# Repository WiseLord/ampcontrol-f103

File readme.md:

# Ampcontrol (STM32F103 / F303 version)

Ampcontrol is an control module for your DIY audio amplifier.
It supports various I²C-controlled audioprocessors and FM tuners.
Also, some other third-party devices are supported.

Some videos related to the device can be found at
[Youtube](https://www.youtube.com/playlist?list=PLfv57leyFFd1C61HgnKE3e_OFIXMBtf-D)

## Hardware support

- Graphic color TFT displays based on various controllers:
  - 160x128: ILI9163, S6D0144, ST7735;
  - 176x132: L2F50126, LPH9157, LS020, SSD1286A;
  - 220x176: HX8340, ILI9225, LGDP4524, S6D0164;
  - 320x240: HX8347A, HX8347D, ILI9320, ILI9341, MC2PA8201, S6D0129, S6D0139, SPFD5408, SSD1289, SSD2119;
  - 400x240: ILI9327, S6D04D1, ST7793;
  - 480x320: HX8357C, ILI9481, ILI9486, R61581, RM68140, ST7796S.

- Audio processors with I²C bus:
  - TDA7439, TDA731X, PT232X, TDA7418, TDA7719.

- FM tuners with I²C bus:
  - RDA580X, SI470X, TEA5767.

- Bluetooth modules
  - CSR8645, BK8000L (GPIO-based control via PCF8574x I²C expander);
  - BT201 (USART-based control).

- USB HID
  - Meida player on the PC can be controlled (Play/Pause and so on) by the device.

- KaRadio and MPD support
  - The device can act as "KaRadio plugin" via USART2 to add web radio support via ESP32. Alternatively, 
it can control MPD server running on Linux (for example, Raspberry PI).

More specific info can be found in [documentation](doc) pages.

## Building the code

[GNU Arm Embedded Toolchain](https://developer.arm.com/tools-and-software/open-source-software/developer-tools/gnu-toolchain/gnu-rm/downloads)
is required to build the project.

The project build system is based on [GNU Make](https://www.gnu.org/software/make/).
Linux users must have it already installed or they can easily do it.
For Windows users there is a port exists.
In both cases, both toolchain and make binaries should be added to the system PATH.

The process of building is very simple and doesn't depend on any other software installed.

### Default build (ILI9341 display with SPI wiring):

`make`

### Build for the specific STM32 MCUs, display and wiring:

`make STM32_MCU=F303CB DISPLAY=R61581 DISPVAR=8BIT`

The list of supported display controllers and MCUs can be found in Makefile or build_all.sh script.

## Schematics and wiring

The schematic and PCB files for the device itself in KiCad format can be found 
in [kicad/ampcontrol-f103](kicad/ampcontrol-f103) directory.

## Useful links

* [Firmware releases](https://github.com/WiseLord/ampcontrol-f103/releases)

* [The article (in Russian)](https://radiokot.ru/artfiles/6484/)

* [Forum thread (in Russian)](https://radiokot.ru/forum/viewtopic.php?f=2&t=158605)

* [Youtube playlist](https://www.youtube.com/playlist?list=PLfv57leyFFd1C61HgnKE3e_OFIXMBtf-D)

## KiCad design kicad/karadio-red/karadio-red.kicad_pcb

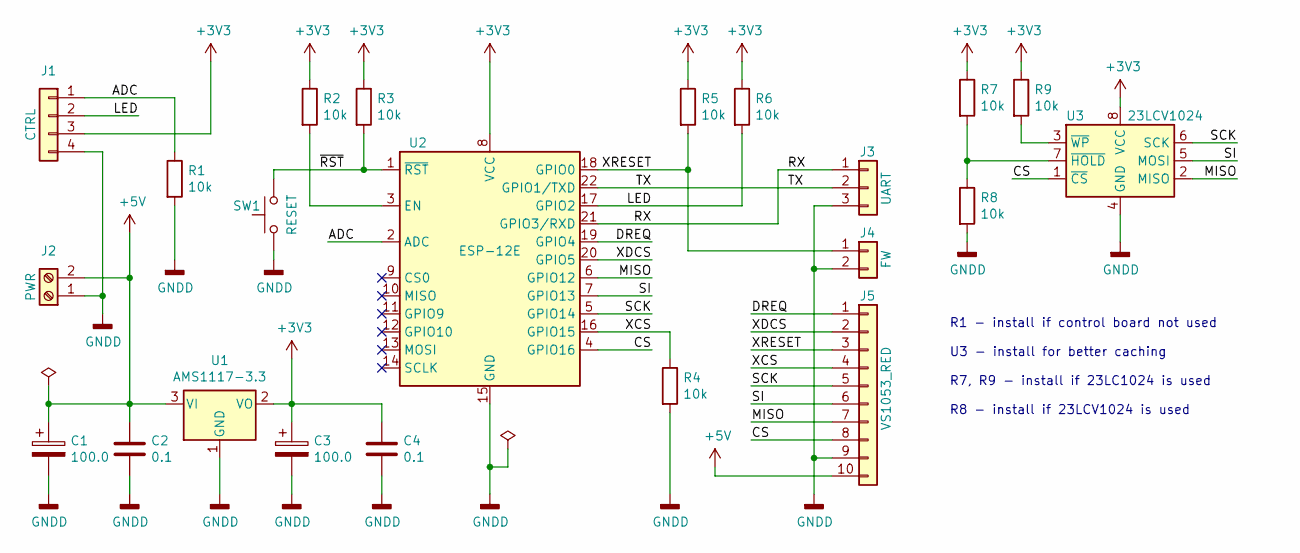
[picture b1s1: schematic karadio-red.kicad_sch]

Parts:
C1, C3: 100.0; CP_Radial_D6.3mm_P2.50mm
C2, C4: 0.1; C_1206_3216Metric
J1: CTRL; PinHeader_1x04_P2.54mm_Vertical
J2: PWR; TerminalBlock_bornier-2_P5.08mm
J3: UART; PinHeader_1x03_P2.54mm_Vertical
J4: FW; PinHeader_1x02_P2.54mm_Vertical
J5: VS1053_RED; PinSocket_1x10_P2.54mm_Vertical
R1, R2, R3, R4, R5, R6, R7, R8, R9: 10k; R_1206_3216Metric
SW1: RESET; SW_PUSH_6mm
U1: AMS1117-3.3; SOT-223-3_TabPin2
U2: ESP-12E
U3: 23LCV1024; SO-8_3.9x4.9mm_P1.27mm

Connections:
+3V3: C3.1, C4.1, J1.3, R2.1, R3.1, R5.1, R6.1, R7.1, R9.1, U1.2 (VO), U2.8 (VCC), U3.8 (VCC)
+5V: C1.1, C2.1, J2.2, J5.10, U1.3 (VI)
/ADC: J1.1, R1.1, U2.2 (ADC)
/CS: J5.8, U2.4 (GPIO16), U3.1 (~CS)
/DREQ: J5.1, U2.19 (GPIO4)
/LED: J1.2, R6.2, U2.17 (GPIO2)
/MISO: J5.7, U2.6 (GPIO12), U3.2 (MISO)
/RX: J3.1, U2.21 (GPIO3/RXD)
/SCK: J5.5, U2.5 (GPIO14), U3.6 (SCK)
/SI: J5.6, U2.7 (GPIO13), U3.5 (MOSI)
/TX: J3.2, U2.22 (GPIO1/TXD)
/XCS: J5.4, R4.1, U2.16 (GPIO15)
/XDCS: J5.2, U2.20 (GPIO5)
/XRESET: J4.1, J5.3, R5.2, U2.18 (GPIO0)
/~RST: R3.2, SW1.2, U2.1 (~RST)
GNDD: C1.2, C2.2, C3.2, C4.2, J1.4, J2.1, J3.3, J4.2, J5.9, R1.2, R4.2, R8.2, SW1.1, U1.1 (GND), U2.15 (GND), U3.4 (GND)
unnamed: R2.2, U2.3 (EN)
unnamed: R7.2, R8.1, U3.7 (~HOLD)
unnamed: R9.2, U3.3 (~WP)

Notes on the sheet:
R1 - install if control board not used U3 - install for better caching R7, R9 - install if 23LC1024 is used R8 - install if 23LCV1024 is used

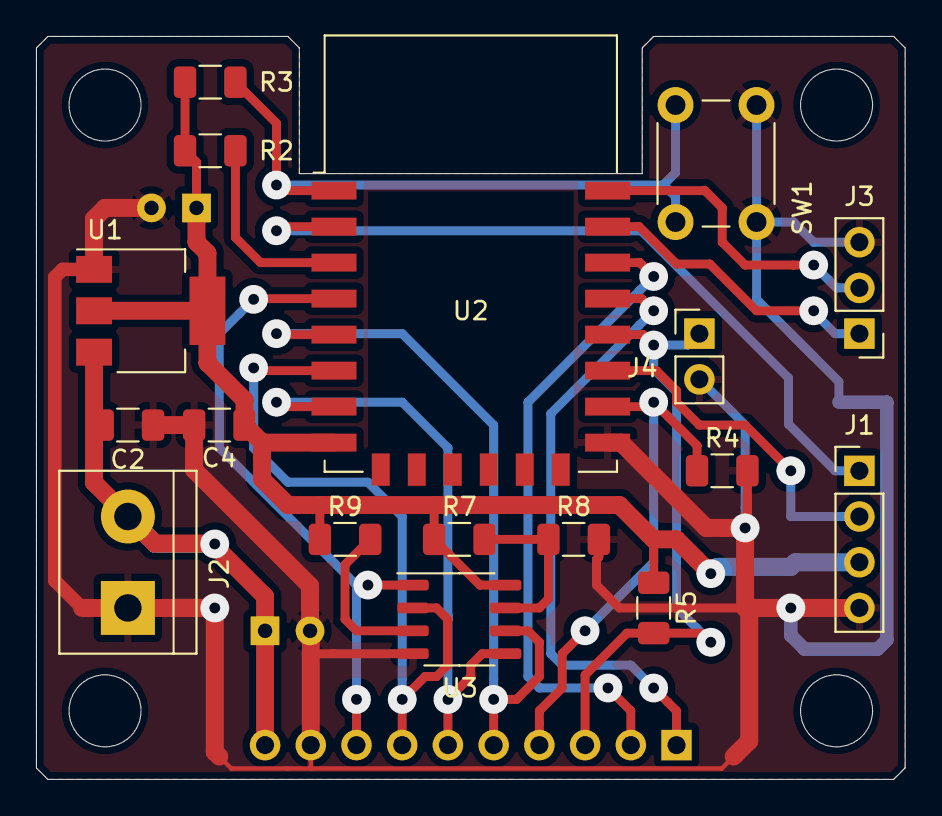
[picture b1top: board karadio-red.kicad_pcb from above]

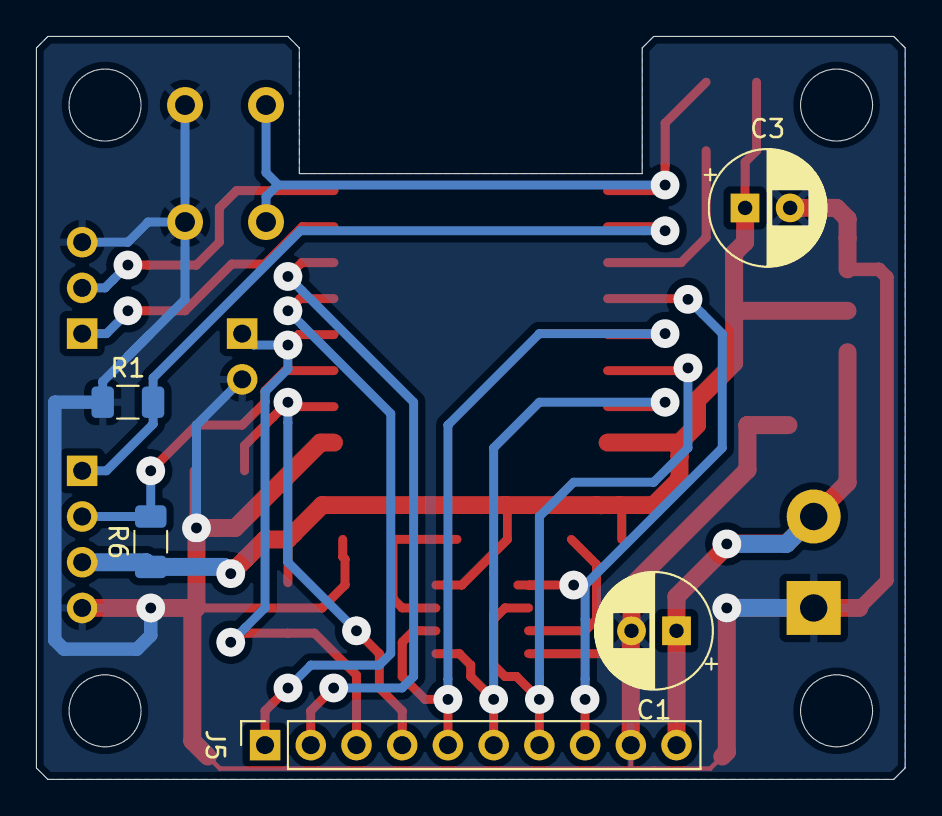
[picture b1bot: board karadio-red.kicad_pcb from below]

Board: 2 copper layers, 48.3 x 41.3 mm, 22 parts (5 on the bottom side), 19 nets.

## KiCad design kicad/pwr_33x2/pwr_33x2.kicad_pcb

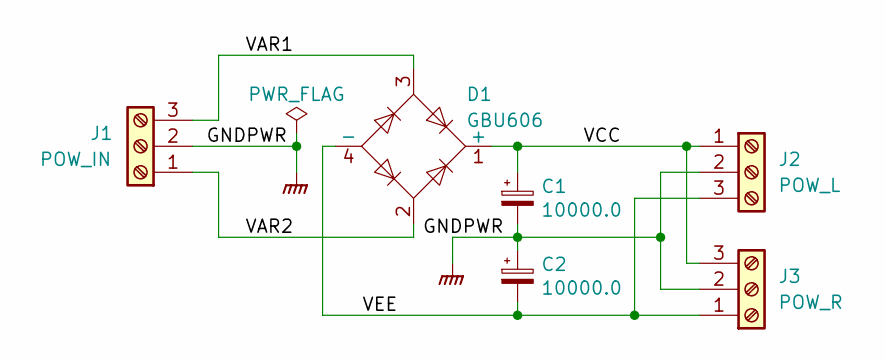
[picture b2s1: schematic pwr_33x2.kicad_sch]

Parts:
C1, C2: 10000.0; CP_Radial_D25.0mm_P10.00mm_SnapIn
D1: GBU606; Diode_Bridge_Vishay_GBU
J1: POW_IN; TerminalBlock_bornier-3_P5.08mm
J2: POW_L; TerminalBlock_bornier-3_P5.08mm
J3: POW_R; TerminalBlock_bornier-3_P5.08mm

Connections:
/VAR1: D1.3, J1.3
/VAR2: D1.2, J1.1
/VCC: C1.1, D1.1 (+), J2.1, J3.3
/VEE: C2.2, D1.4 (-), J2.3, J3.1
GNDPWR: C1.2, C2.1, J1.2, J2.2, J3.2

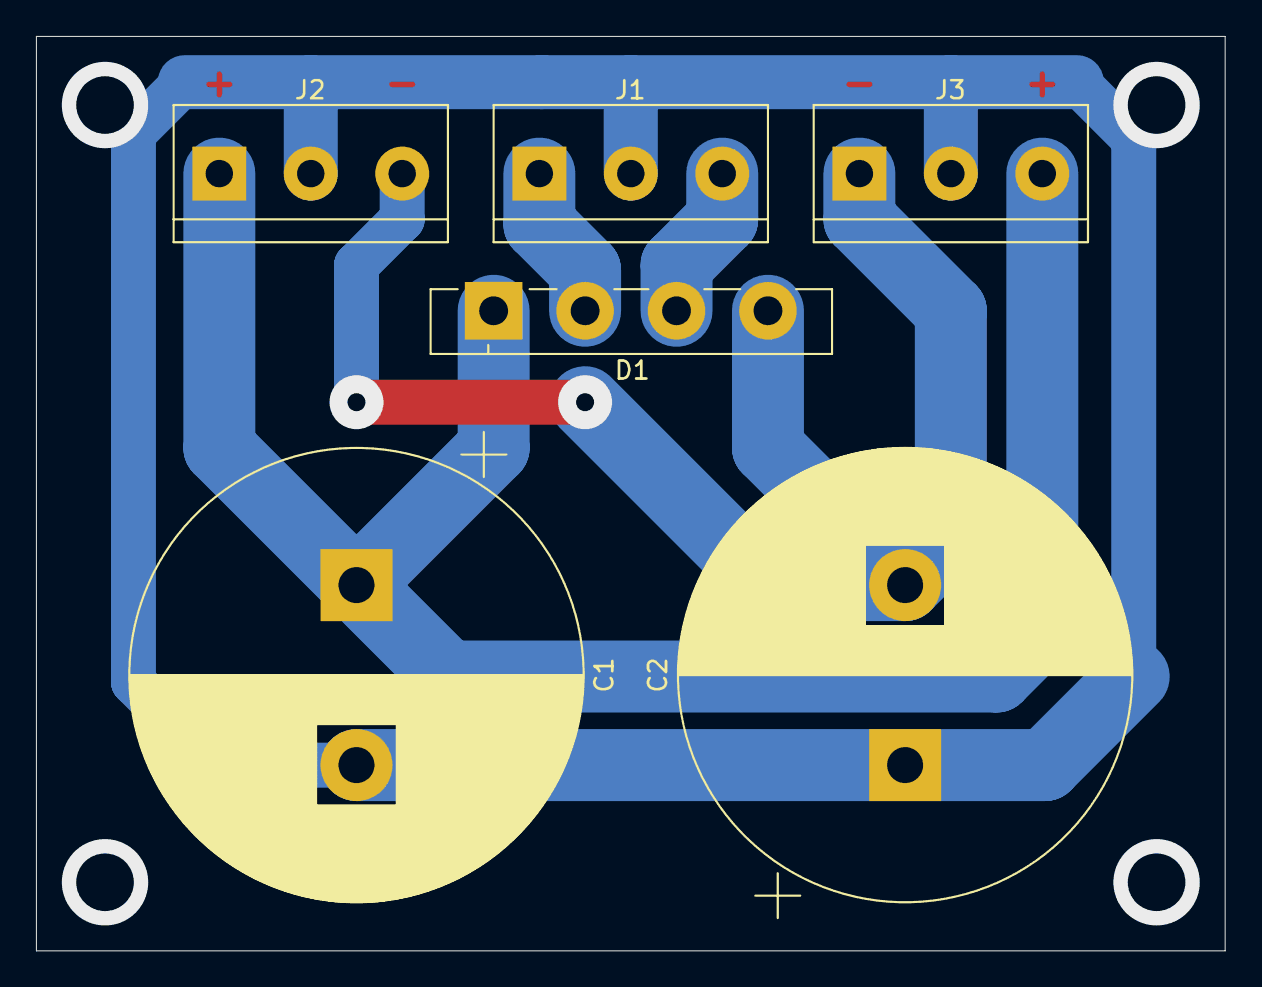
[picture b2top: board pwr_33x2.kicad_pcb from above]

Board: 2 copper layers, 66.0 x 50.8 mm, 6 parts (0 on the bottom side), 5 nets.

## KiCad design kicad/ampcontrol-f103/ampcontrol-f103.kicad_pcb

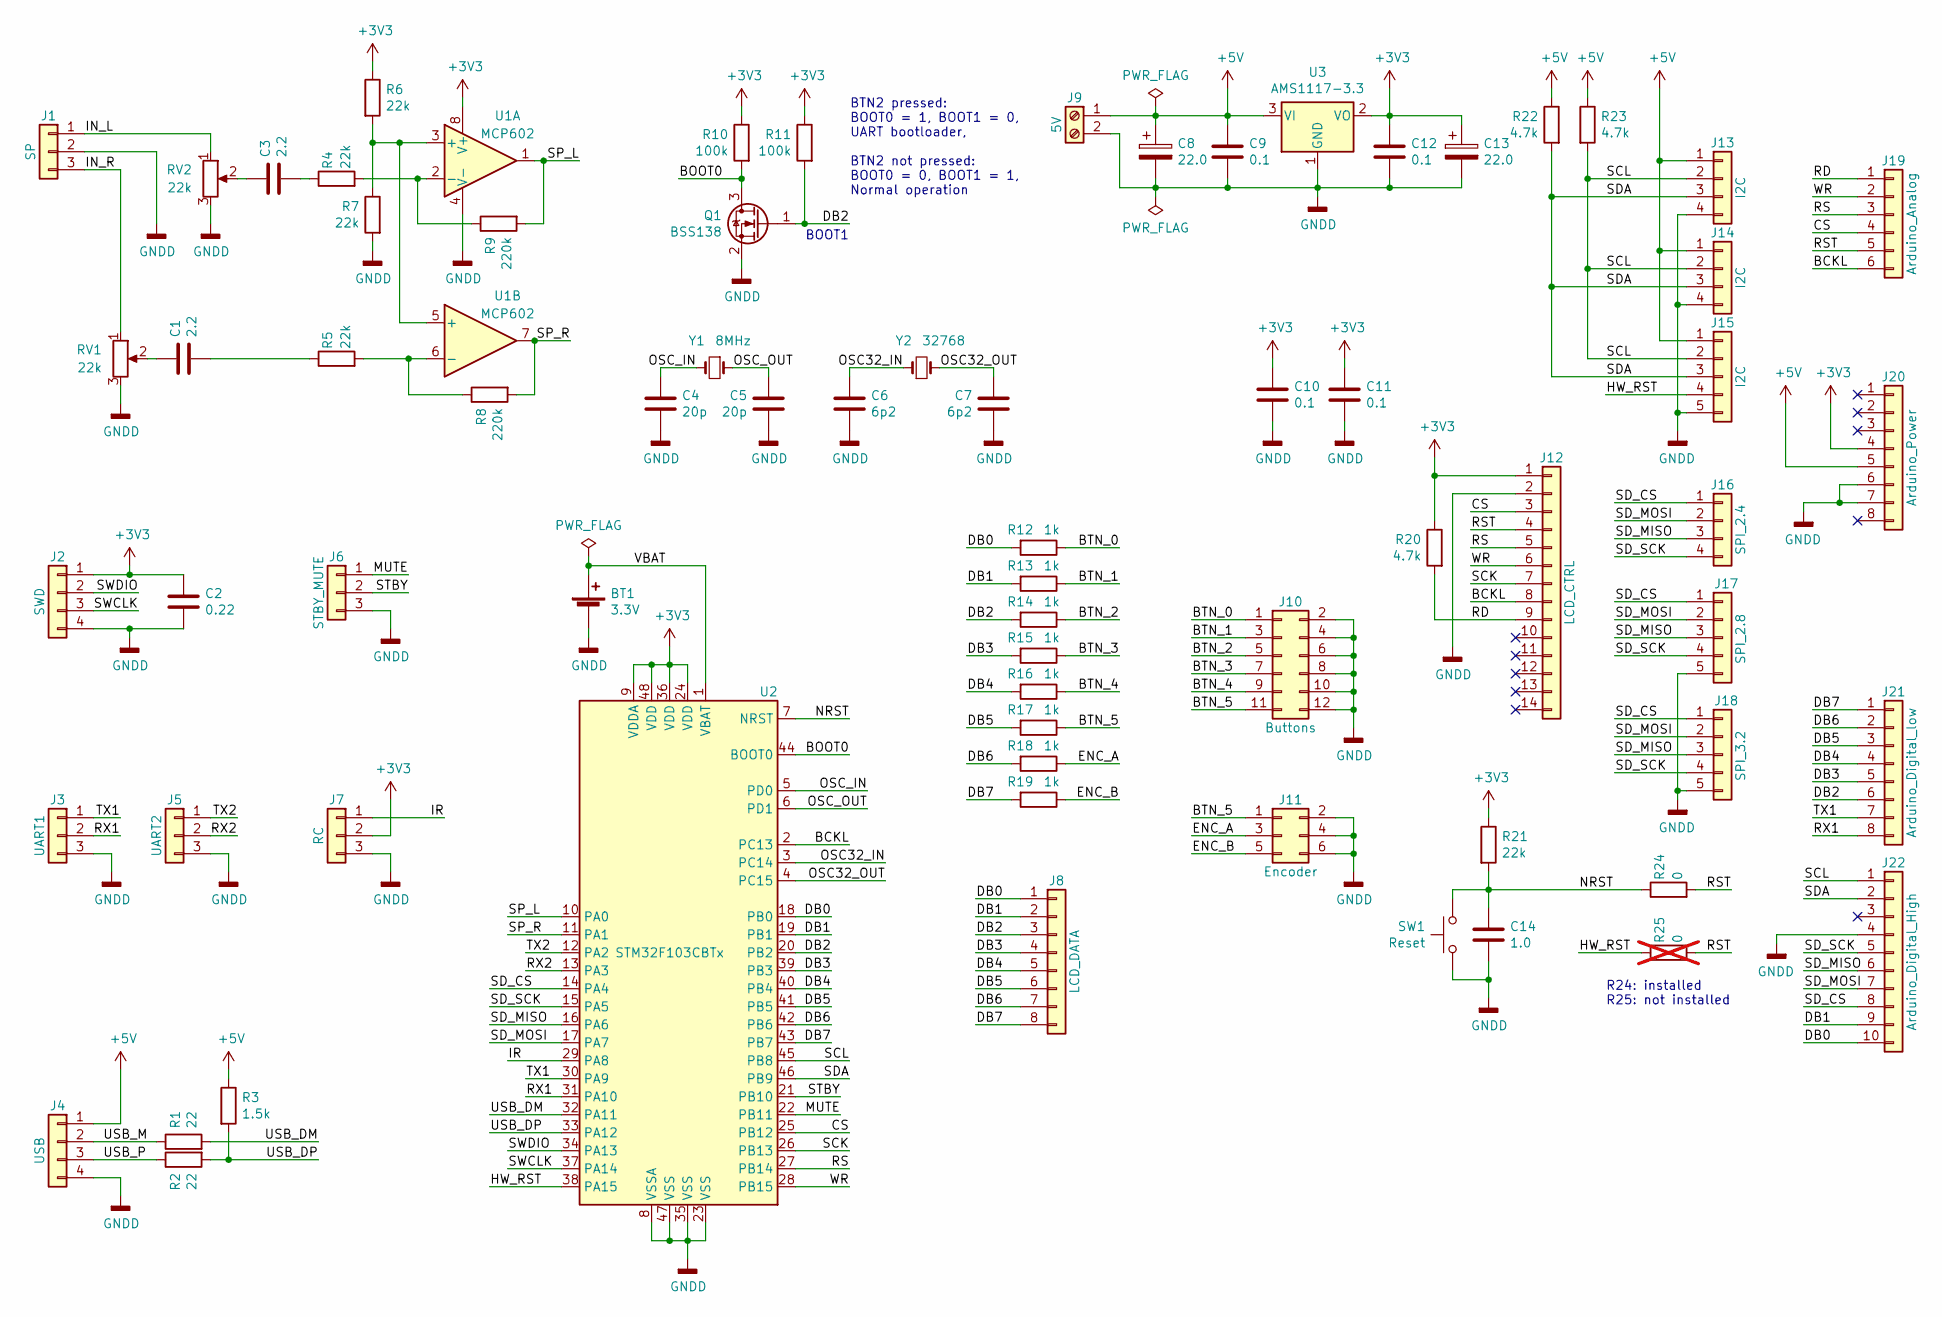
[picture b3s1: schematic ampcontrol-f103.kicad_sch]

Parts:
BT1: 3.3V; CR1220
C1, C3: 2.2; C_0805_2012Metric
C2: 0.22; C_0805_2012Metric
C4, C5: 20p; C_0805_2012Metric
C6, C7: 6p2; C_0805_2012Metric
C8, C13: 22.0; CP_EIA-6032-28_Kemet-C
C9, C10, C11, C12: 0.1; C_0805_2012Metric
C14: 1.0; C_0805_2012Metric
J1: SP; PinHeader_1x03_P2.54mm_Vertical
J2: SWD; PinHeader_1x04_P2.54mm_Vertical
J3: UART1; PinHeader_1x03_P2.54mm_Vertical
J4: USB; PinHeader_1x04_P2.54mm_Vertical
J5: UART2; PinHeader_1x03_P2.54mm_Vertical
J6: STBY_MUTE; PinHeader_1x03_P2.54mm_Vertical
J7: RC; PinHeader_1x03_P2.54mm_Vertical
J8: LCD_DATA; PinSocket_1x08_P2.54mm_Vertical
J9: 5V; TerminalBlock_bornier-2_P5.08mm
J10: Buttons; PinHeader_2x06_P2.54mm_Vertical
J11: Encoder; PinHeader_2x03_P2.54mm_Vertical
J12: LCD_CTRL; PinSocket_1x14_P2.54mm_Vertical
J13, J14: I2C; PinHeader_1x04_P2.54mm_Vertical
J15: I2C; PinHeader_1x05_P2.54mm_Vertical
J16: SPI_2.4; PinSocket_1x04_P2.54mm_Vertical
J17: SPI_2.8; PinSocket_1x05_P2.54mm_Vertical
J18: SPI_3.2; PinSocket_1x05_P2.54mm_Vertical
J19: Arduino_Analog; PinSocket_1x06_P2.54mm_Vertical
J20: Arduino_Power; PinSocket_1x08_P2.54mm_Vertical
J21: Arduino_Digital_low; PinSocket_1x08_P2.54mm_Vertical
J22: Arduino_Digital_High; PinSocket_1x10_P2.54mm_Vertical
Q1: BSS138; SOT-23
R1, R2: 22; R_0805_2012Metric
R3: 1.5k; R_0805_2012Metric
R4, R5, R6, R7, R21: 22k; R_0805_2012Metric
R8, R9: 220k; R_0805_2012Metric
R10, R11: 100k; R_0805_2012Metric
R12, R13, R14, R15, R16, R17, R18, R19: 1k; R_0805_2012Metric
R20, R22, R23: 4.7k; R_0805_2012Metric
R24: 0; R_0805_2012Metric
R25: 0; R_0805_2012Metric; not fitted
RV1, RV2: 22k; Potentiometer_Piher_PT-6-V_Vertical
SW1: Reset; SW_PUSH_6mm
U1: MCP602; SOIC-8_3.9x4.9mm_P1.27mm
U2: STM32F103CBTx; LQFP-48_7x7mm_P0.5mm
U3: AMS1117-3.3; SOT-223-3_TabPin2
Y1: 8MHz; Crystal_HC49-4H_Vertical
Y2: 32768; Crystal_C38-LF_D3.0mm_L8.0mm_Vertical

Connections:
+3V3: C2.1, C10.2, C11.2, C12.2, C13.1, J2.1, J7.2, J12.1, J20.4, R6.1, R10.1, R11.1, R20.1, R21.1, U1.8 (V+), U2.9 (VDDA), U2.24 (VDD), U2.36 (VDD), U2.48 (VDD), U3.2 (VO)
+5V: C8.1, C9.2, J4.1, J9.1, J13.1, J14.1, J15.1, J20.5, R3.1, R22.1, R23.1, U3.3 (VI)
/BCKL: J12.8, J19.6, U2.2 (PC13)
/BOOT0: Q1.3 (D), R10.2, U2.44 (BOOT0)
/BTN_0: J10.1, R12.1
/BTN_1: J10.3, R13.1
/BTN_2: J10.5, R14.1
/BTN_3: J10.7, R15.1
/BTN_4: J10.9, R16.1
/BTN_5: J10.11, J11.1, R17.1
/CS: J12.3, J19.4, U2.25 (PB12)
/DB0: J8.1, J22.10, R12.2, U2.18 (PB0)
/DB1: J8.2, J22.9, R13.2, U2.19 (PB1)
/DB2: J8.3, J21.6, Q1.1 (G), R11.2, R14.2, U2.20 (PB2)
/DB3: J8.4, J21.5, R15.2, U2.39 (PB3)
/DB4: J8.5, J21.4, R16.2, U2.40 (PB4)
/DB5: J8.6, J21.3, R17.2, U2.41 (PB5)
/DB6: J8.7, J21.2, R18.2, U2.42 (PB6)
/DB7: J8.8, J21.1, R19.2, U2.43 (PB7)
/ENC_A: J11.3, R18.1
/ENC_B: J11.5, R19.1
/HW_RST: J15.4, R25.1, U2.38 (PA15)
/IN_L: J1.1, RV2.1
/IN_R: J1.3, RV1.1
/IR: J7.1, U2.29 (PA8)
/MUTE: J6.1, U2.22 (PB11)
/NRST: C14.2, R21.2, R24.1, SW1.1, U2.7 (NRST)
/OSC32_IN: C6.1, U2.3 (PC14), Y2.1
/OSC32_OUT: C7.2, U2.4 (PC15), Y2.2
/OSC_IN: C4.1, U2.5 (PD0), Y1.2
/OSC_OUT: C5.2, U2.6 (PD1), Y1.1
/RD: J12.9, J19.1, R20.2
/RS: J12.5, J19.3, U2.27 (PB14)
/RST: J12.4, J19.5, R24.2, R25.2
/RX1: J3.2, J21.8, U2.31 (PA10)
/RX2: J5.2, U2.13 (PA3)
/SCK: J12.7, U2.26 (PB13)
/SCL: J13.2, J14.2, J15.2, J22.1, R23.2, U2.45 (PB8)
/SDA: J13.3, J14.3, J15.3, J22.2, R22.2, U2.46 (PB9)
/SD_CS: J16.1, J17.1, J18.1, J22.8, U2.14 (PA4)
/SD_MISO: J16.3, J17.3, J18.3, J22.6, U2.16 (PA6)
/SD_MOSI: J16.2, J17.2, J18.2, J22.7, U2.17 (PA7)
/SD_SCK: J16.4, J17.4, J18.4, J22.5, U2.15 (PA5)
/SP_L: R9.2, U1.1, U2.10 (PA0)
/SP_R: R8.2, U1.7, U2.11 (PA1)
/STBY: J6.2, U2.21 (PB10)
/SWCLK: J2.3, U2.37 (PA14)
/SWDIO: J2.2, U2.34 (PA13)
/TX1: J3.1, J21.7, U2.30 (PA9)
/TX2: J5.1, U2.12 (PA2)
/USB_DM: R1.2, U2.32 (PA11)
/USB_DP: R2.2, R3.2, U2.33 (PA12)
/USB_M: J4.2, R1.1
/USB_P: J4.3, R2.1
/VBAT: BT1.1 (+), U2.1 (VBAT)
/WR: J12.6, J19.2, U2.28 (PB15)
GNDD: BT1.2 (-), C2.2, C4.2, C5.1, C6.2, C7.1, C8.2, C9.1, C10.1, C11.1, C12.1, C13.2, C14.1, J1.2, J2.4, J3.3, J4.4, J5.3, J6.3, J7.3, J9.2, J10.2, J10.4, J10.6, J10.8, J10.10, J10.12, J11.2, J11.4, J11.6, J12.2, J13.4, J14.4, J15.5, J17.5, J18.5, J20.6, J20.7, J22.4, Q1.2 (S), R7.2, RV1.3, RV2.3, SW1.2, U1.4 (V-), U2.8 (VSSA), U2.23 (VSS), U2.35 (VSS), U2.47 (VSS), U3.1 (GND)
unnamed: C1.1, R5.1
unnamed: C1.2, RV1.2
unnamed: C3.1, R4.1
unnamed: C3.2, RV2.2
unnamed: R4.2, R9.1, U1.2 (-)
unnamed: R5.2, R8.1, U1.6 (-)
unnamed: R6.2, R7.1, U1.3 (+), U1.5 (+)

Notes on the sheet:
R24: installed R25: not installed
BOOT1
BTN2 pressed: BOOT0 = 1, BOOT1 = 0, UART bootloader, BTN2 not pressed: BOOT0 = 0, BOOT1 = 1, Normal operation

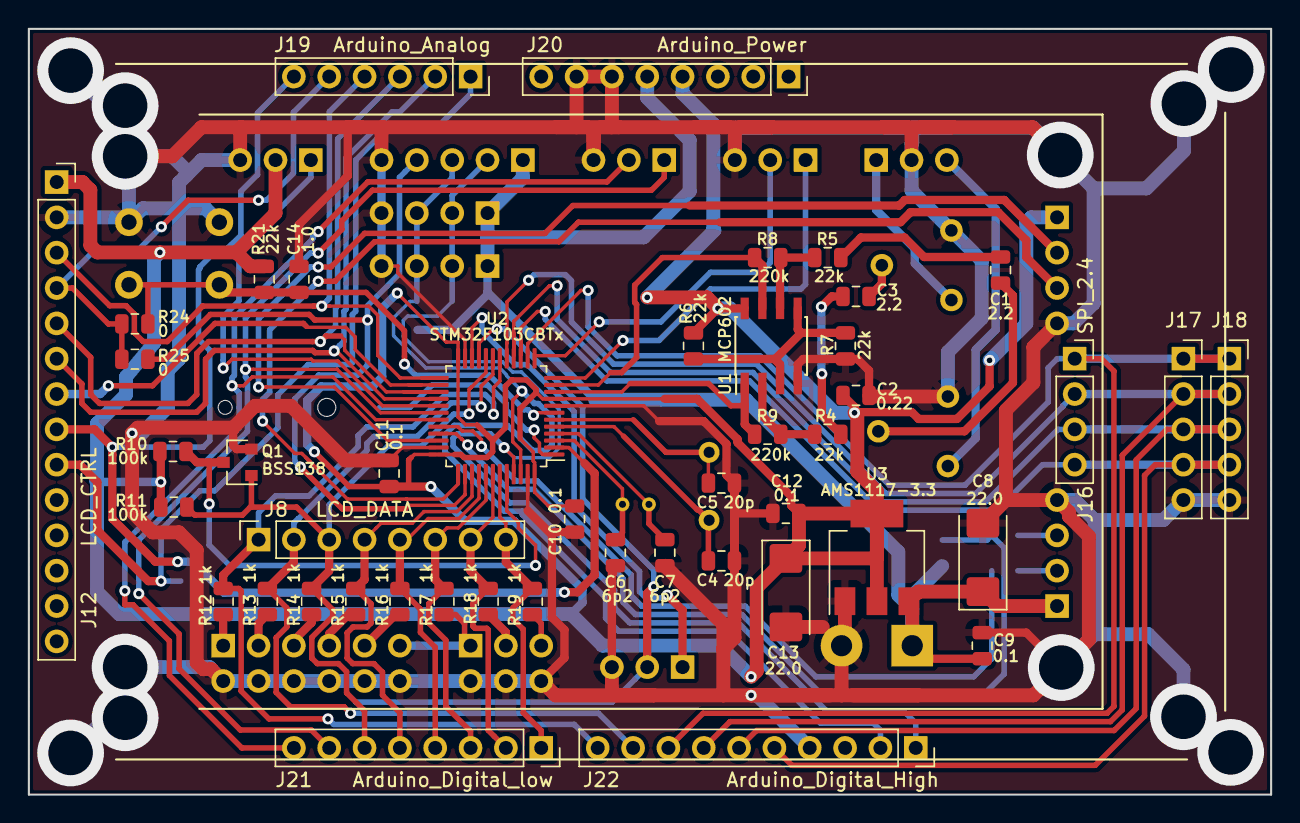
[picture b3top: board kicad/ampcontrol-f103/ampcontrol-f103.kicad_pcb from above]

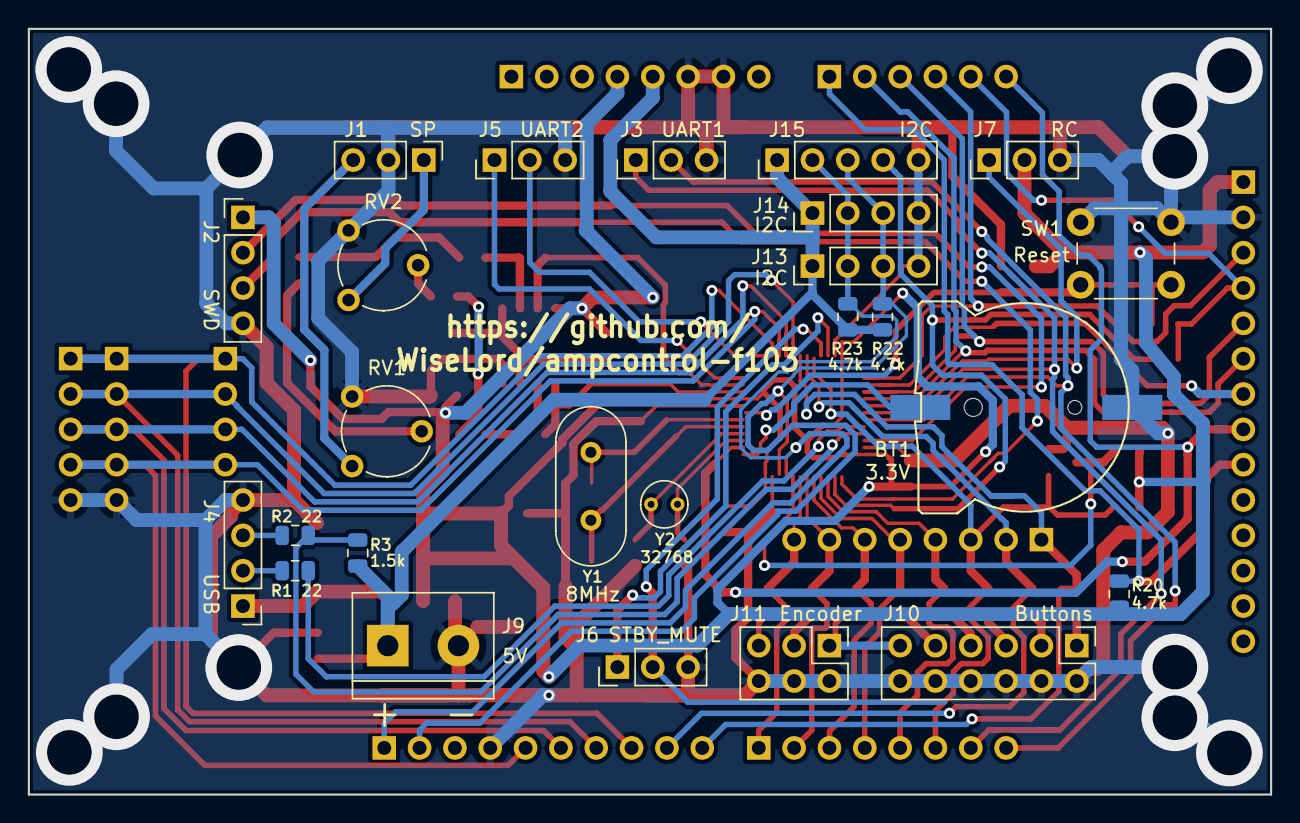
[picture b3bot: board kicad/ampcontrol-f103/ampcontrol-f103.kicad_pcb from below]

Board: 2 copper layers, 89.3 x 55.0 mm, 71 parts (25 on the bottom side), 64 nets.

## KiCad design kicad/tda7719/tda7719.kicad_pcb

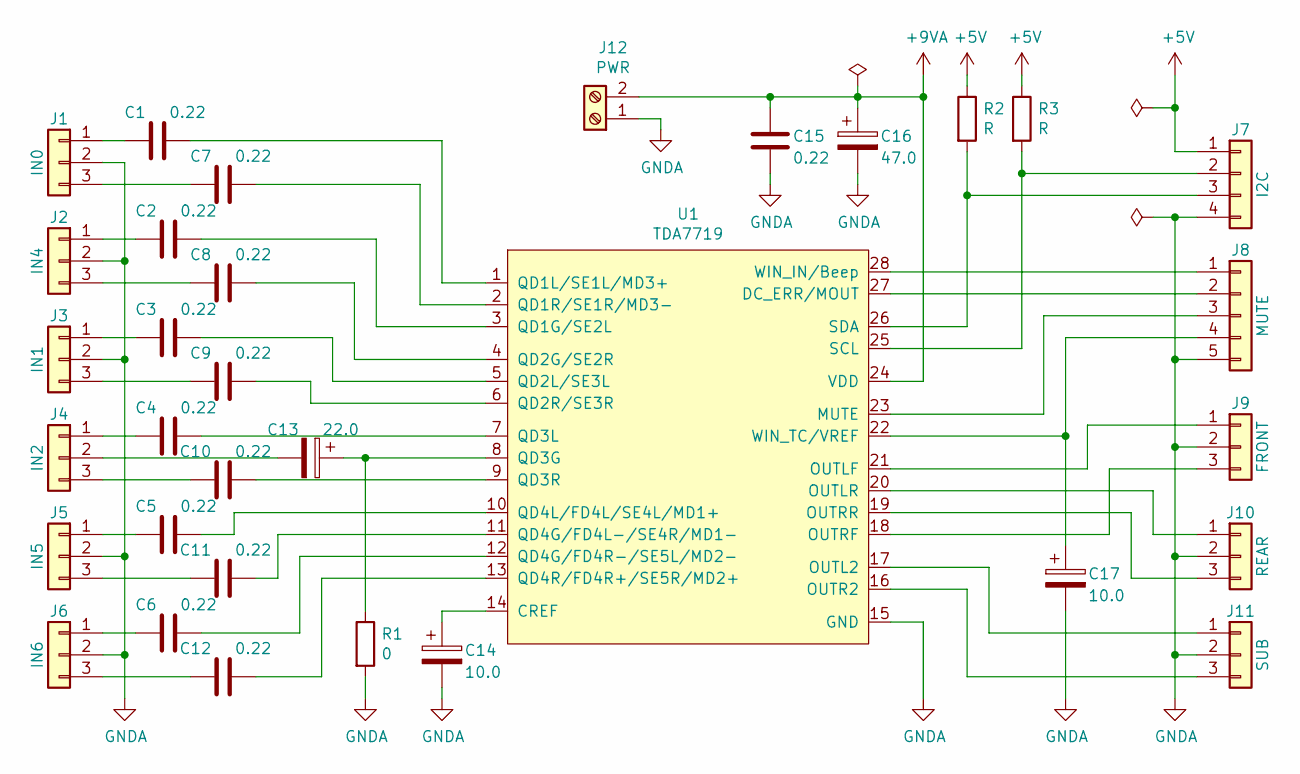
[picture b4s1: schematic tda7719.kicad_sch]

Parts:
C1, C2, C3, C4, C5, C6, C7, C8, C9, C10, C11, C12, C15: 0.22; C_1206_3216Metric_Pad1.42x1.75mm_HandSolder
C13: 22.0; CP_Radial_D5.0mm_P2.50mm
C14, C17: 10.0; CP_Radial_D5.0mm_P2.50mm
C16: 47.0; CP_Radial_D5.0mm_P2.50mm
J1: IN0; PinHeader_1x03_P2.54mm_Vertical
J2: IN4; PinHeader_1x03_P2.54mm_Vertical
J3: IN1; PinHeader_1x03_P2.54mm_Vertical
J4: IN2; PinHeader_1x03_P2.54mm_Vertical
J5: IN5; PinHeader_1x03_P2.54mm_Vertical
J6: IN6; PinHeader_1x03_P2.54mm_Vertical
J7: I2C; PinHeader_1x04_P2.54mm_Vertical
J8: MUTE; PinHeader_1x05_P2.54mm_Vertical
J9: FRONT; PinHeader_1x03_P2.54mm_Vertical
J10: REAR; PinHeader_1x03_P2.54mm_Vertical
J11: SUB; PinHeader_1x03_P2.54mm_Vertical
J12: PWR; TerminalBlock_Phoenix_MKDS-1,5-2-5.08_1x02_P5.08mm_Horizont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
R1: 0; R_1206_3216Metric_Pad1.42x1.75mm_HandSolder
R2, R3: R; R_1206_3216Metric_Pad1.42x1.75mm_HandSolder
U1: TDA7719; TSSOP-28_4.4x9.7mm_P0.65mm

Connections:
+5V: J7.1, R2.1, R3.1
+9VA: C15.2, C16.1, J12.2, U1.24 (VDD)
GNDA: C14.2, C15.1, C16.2, C17.2, J1.2, J2.2, J3.2, J5.2, J6.2, J7.4, J8.5, J9.2, J10.2, J11.2, J12.1, R1.2, U1.15 (GND)
unnamed: C1.1, U1.1 (QD1L/SE1L/MD3+)
unnamed: C1.2, J1.1
unnamed: C2.1, U1.3 (QD1G/SE2L)
unnamed: C2.2, J2.1
unnamed: C3.1, U1.5 (QD2L/SE3L)
unnamed: C3.2, J3.1
unnamed: C4.1, U1.7 (QD3L)
unnamed: C4.2, J4.1
unnamed: C5.1, U1.10 (QD4L/FD4L/SE4L/MD1+)
unnamed: C5.2, J5.1
unnamed: C6.1, U1.12 (QD4G/FD4R-/SE5L/MD2-)
unnamed: C6.2, J6.1
unnamed: C7.1, U1.2 (QD1R/SE1R/MD3-)
unnamed: C7.2, J1.3
unnamed: C8.1, U1.4 (QD2G/SE2R)
unnamed: C8.2, J2.3
unnamed: C9.1, U1.6 (QD2R/SE3R)
unnamed: C9.2, J3.3
unnamed: C10.1, U1.9 (QD3R)
unnamed: C10.2, J4.3
unnamed: C11.1, U1.11 (QD4G/FD4L-/SE4R/MD1-)
unnamed: C11.2, J5.3
unnamed: C12.1, U1.13 (QD4R/FD4R+/SE5R/MD2+)
unnamed: C12.2, J6.3
unnamed: C13.1, R1.1, U1.8 (QD3G)
unnamed: C13.2, J4.2
unnamed: C14.1, U1.14 (CREF)
unnamed: C17.1, J8.4, U1.22 (WIN_TC/VREF)
unnamed: J7.2, R3.2, U1.25 (SCL)
unnamed: J7.3, R2.2, U1.26 (SDA)
unnamed: J8.1, U1.28 (WIN_IN/Beep)
unnamed: J8.2, U1.27 (DC_ERR/MOUT)
unnamed: J8.3, U1.23 (MUTE)
unnamed: J9.1, U1.21 (OUTLF)
unnamed: J9.3, U1.18 (OUTRF)
unnamed: J10.1, U1.20 (OUTLR)
unnamed: J10.3, U1.19 (OUTRR)
unnamed: J11.1, U1.17 (OUTL2)
unnamed: J11.3, U1.16 (OUTR2)

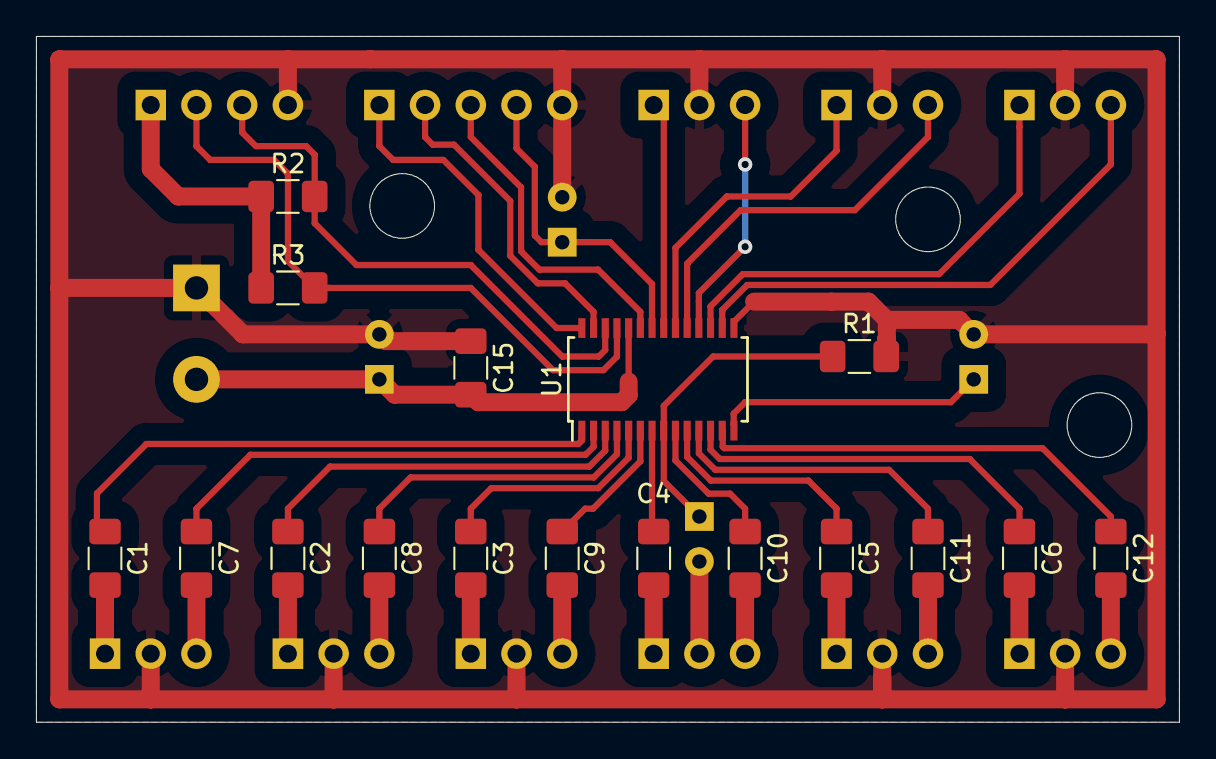
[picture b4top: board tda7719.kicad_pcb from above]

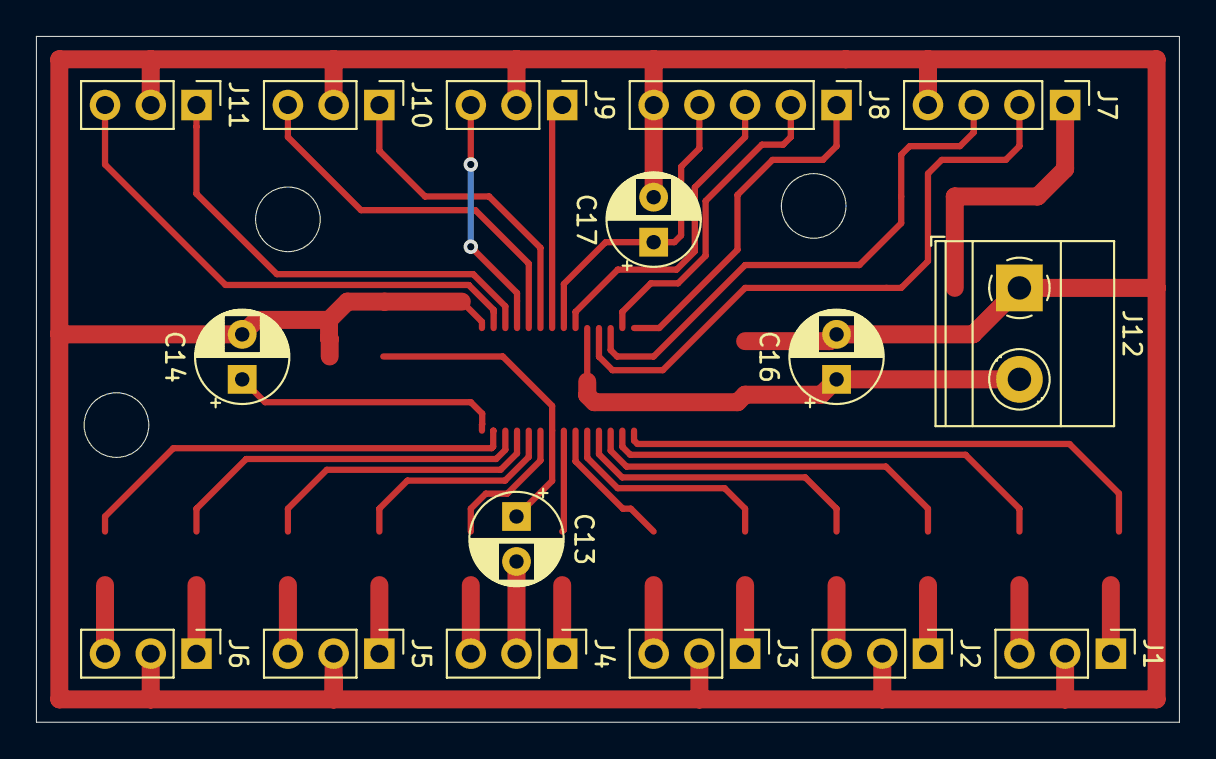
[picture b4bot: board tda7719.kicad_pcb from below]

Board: 2 copper layers, 63.5 x 38.1 mm, 33 parts (16 on the bottom side), 42 nets.

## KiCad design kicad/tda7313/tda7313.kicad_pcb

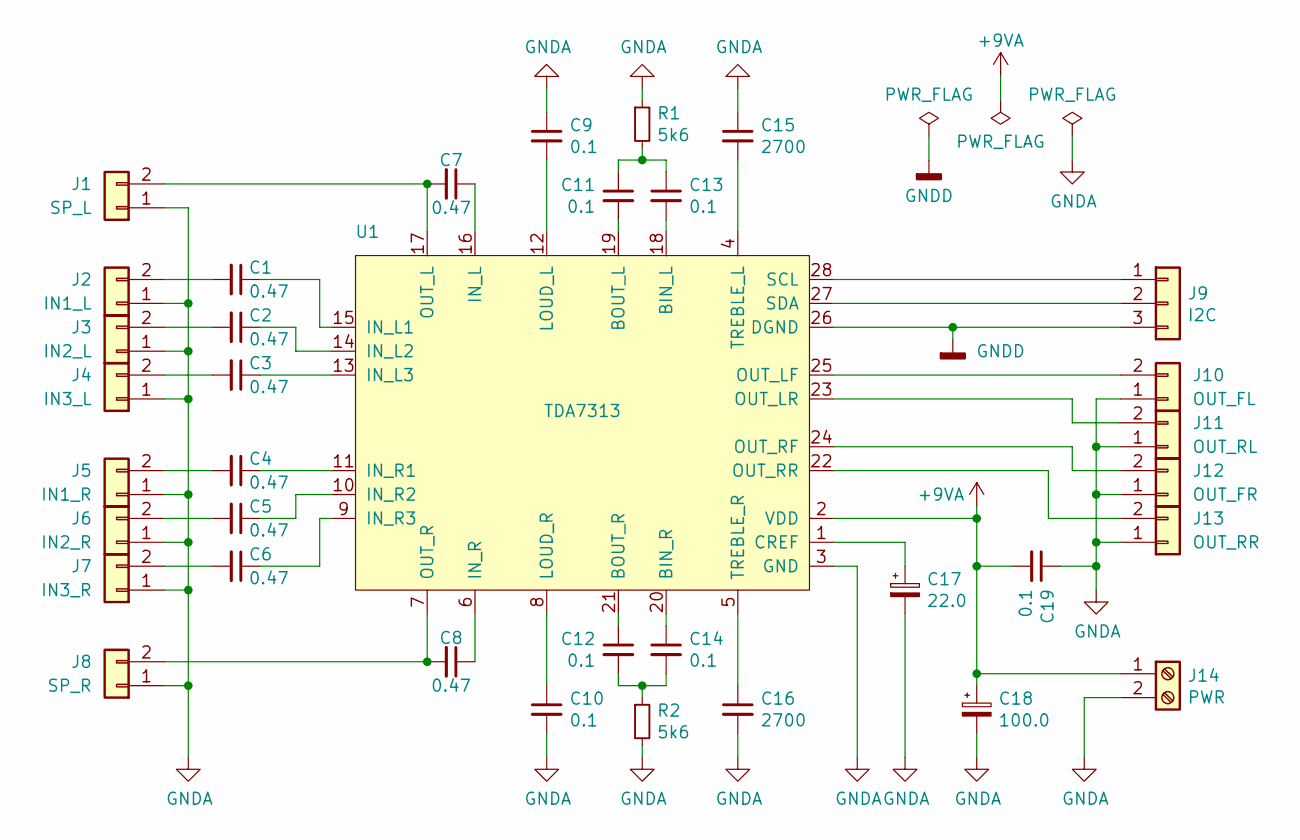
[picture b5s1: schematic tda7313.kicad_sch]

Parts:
C1, C2, C3, C4, C5, C6, C7, C8: 0.47; C_Rect_L13.0mm_W8.0mm_P10.00mm_FKS3_FKP3_MKS4
C9, C10, C11, C12, C13, C14: 0.1; C_Rect_L13.0mm_W4.0mm_P10.00mm_FKS3_FKP3_MKS4
C15, C16: 2700; C_Disc_D4.7mm_W2.5mm_P5.00mm
C17: 22.0; CP_Radial_D6.3mm_P2.50mm
C18: 100.0; CP_Radial_D6.3mm_P2.50mm
C19: 0.1; C_1206_3216Metric_Pad1.42x1.75mm_HandSolder
J1: SP_L; PinHeader_1x02_P2.54mm_Vertical
J2: IN1_L; PinHeader_1x02_P2.54mm_Vertical
J3: IN2_L; PinHeader_1x02_P2.54mm_Vertical
J4: IN3_L; PinHeader_1x02_P2.54mm_Vertical
J5: IN1_R; PinHeader_1x02_P2.54mm_Vertical
J6: IN2_R; PinHeader_1x02_P2.54mm_Vertical
J7: IN3_R; PinHeader_1x02_P2.54mm_Vertical
J8: SP_R; PinHeader_1x02_P2.54mm_Vertical
J9: I2C; PinHeader_1x03_P2.54mm_Vertical
J10: OUT_FL; PinHeader_1x02_P2.54mm_Vertical
J11: OUT_RL; PinHeader_1x02_P2.54mm_Vertical
J12: OUT_FR; PinHeader_1x02_P2.54mm_Vertical
J13: OUT_RR; PinHeader_1x02_P2.54mm_Vertical
J14: PWR; TerminalBlock_Phoenix_MKDS-1,5-2-5.08_1x02_P5.08mm_Horizont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
R1, R2: 5k6; R_1206_3216Metric_Pad1.42x1.75mm_HandSolder
U1: TDA7313; SOIC-28W_7.5x17.9mm_P1.27mm

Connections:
+9VA: C18.1, C19.2, J14.1, U1.2 (VDD)
GNDA: C9.1, C10.2, C15.1, C16.2, C17.2, C18.2, C19.1, J1.1, J2.1, J3.1, J4.1, J5.1, J6.1, J7.1, J8.1, J10.1, J11.1, J12.1, J13.1, J14.2, R1.1, R2.2, U1.3 (GND)
GNDD: J9.3, U1.26 (DGND)
unnamed: C1.1, U1.15 (IN_L1)
unnamed: C1.2, J2.2
unnamed: C2.1, U1.14 (IN_L2)
unnamed: C2.2, J3.2
unnamed: C3.1, U1.13 (IN_L3)
unnamed: C3.2, J4.2
unnamed: C4.1, U1.11 (IN_R1)
unnamed: C4.2, J5.2
unnamed: C5.1, U1.10 (IN_R2)
unnamed: C5.2, J6.2
unnamed: C6.1, U1.9 (IN_R3)
unnamed: C6.2, J7.2
unnamed: C7.1, U1.16 (IN_L)
unnamed: C7.2, J1.2, U1.17 (OUT_L)
unnamed: C8.1, U1.6 (IN_R)
unnamed: C8.2, J8.2, U1.7 (OUT_R)
unnamed: C9.2, U1.12 (LOUD_L)
unnamed: C10.1, U1.8 (LOUD_R)
unnamed: C11.1, C13.1, R1.2
unnamed: C11.2, U1.19 (BOUT_L)
unnamed: C12.1, U1.21 (BOUT_R)
unnamed: C12.2, C14.2, R2.1
unnamed: C13.2, U1.18 (BIN_L)
unnamed: C14.1, U1.20 (BIN_R)
unnamed: C15.2, U1.4 (TREBLE_L)
unnamed: C16.1, U1.5 (TREBLE_R)
unnamed: C17.1, U1.1 (CREF)
unnamed: J9.1, U1.28 (SCL)
unnamed: J9.2, U1.27 (SDA)
unnamed: J10.2, U1.25 (OUT_LF)
unnamed: J11.2, U1.23 (OUT_LR)
unnamed: J12.2, U1.24 (OUT_RF)
unnamed: J13.2, U1.22 (OUT_RR)
